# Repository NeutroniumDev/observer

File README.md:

# Observer
Observer is a device that measures the altitude, acceleration, rotation, and location of model rockets. 

As of June 24, 2022, Observer's schematic is complete-ish but untested. It uses the following chips:
- SAMD21G18   (Processing)
- USB-C port (data transfer
  + Protection IC (can be omitted) 
- ISM330         (Rotation and low-acceleration measurements)
- BMP390        (Pressure-based altitude measurements)
- ADXL375          (High-acceleration measurements)
- Micro SD card      (Temporary data storage)
- Ublox MAX M8     (GPS)
  + External LNA
- RFM97C         (LoRa Radio tranceiver)
- PCA9685PW     (LED driver, used as motor driver.)

Future changes (maybe):
-Change the pogo pin pads to headers for easier debugging, and the JTAG pads to
a full JTAG connector.
-Change the logo on the back of the PCB because I won't be using it for the TARC 
competition anymore. 
-Remove the USB-C anti-static protection IC, because it costs money and is most
likely useless.
-Remove a lot of decoupling caps, because I don't really need them
-Find a better way of controlling the servo motors, maybe through connecting them
to GPIO and using a level shifter

**Notes:**

As of June 24th, 2022 the design has not been fully validated. I don't have a 
JTAG debugger and I can't get one right now, so I cant upload a bootloader to upload
code over USB. From what I can tell the voltages look fine and the power management 
works perfectly, but I have not been able to test anything else. Plus, since most of
the schematic is based on reference designs, I see no reason why things *shouldn't*
work. 

To build this for myself I substituted the ISM330 with its non-industrial variant, the
LSM6DSO32. In retrospect I realize that the ISM330 was overkill, and using the LSM6DSO32 
makes the secondary high-g accelerometer redundant in most use cases, since the LSM6 can
already go up to 32G. So, if you're looking to build this for yourself, just get the LSM6
and skip the ADXL375, it will save you ~12 bucks. 

More retrospect: the LNA is probably also not very useful, since when used with
rockets the GPS basically has clear view of the sky with very little blocking the signal, 
apart from maybe the rocket casing, but that's insignificant. If you're building this for yourself, 
you can omit the LNA, but MAKE SURE you change the schematic and board layout so that 
the gps module connects directly to the u.fl connector. The GPS will not work otherwise. 
The LNA also has some really fine pitch pins, so the risk of shorting contacts 
is pretty high. So be careful!

As for the name, 'observer' is staying for now since I can't really think of anything
else. Suggestions would be much appreciated! 

This project is licensed under the GNU General Public License v3.0.
Please use responsibly. You *can* make a missle with this, but that doesn't mean you should.

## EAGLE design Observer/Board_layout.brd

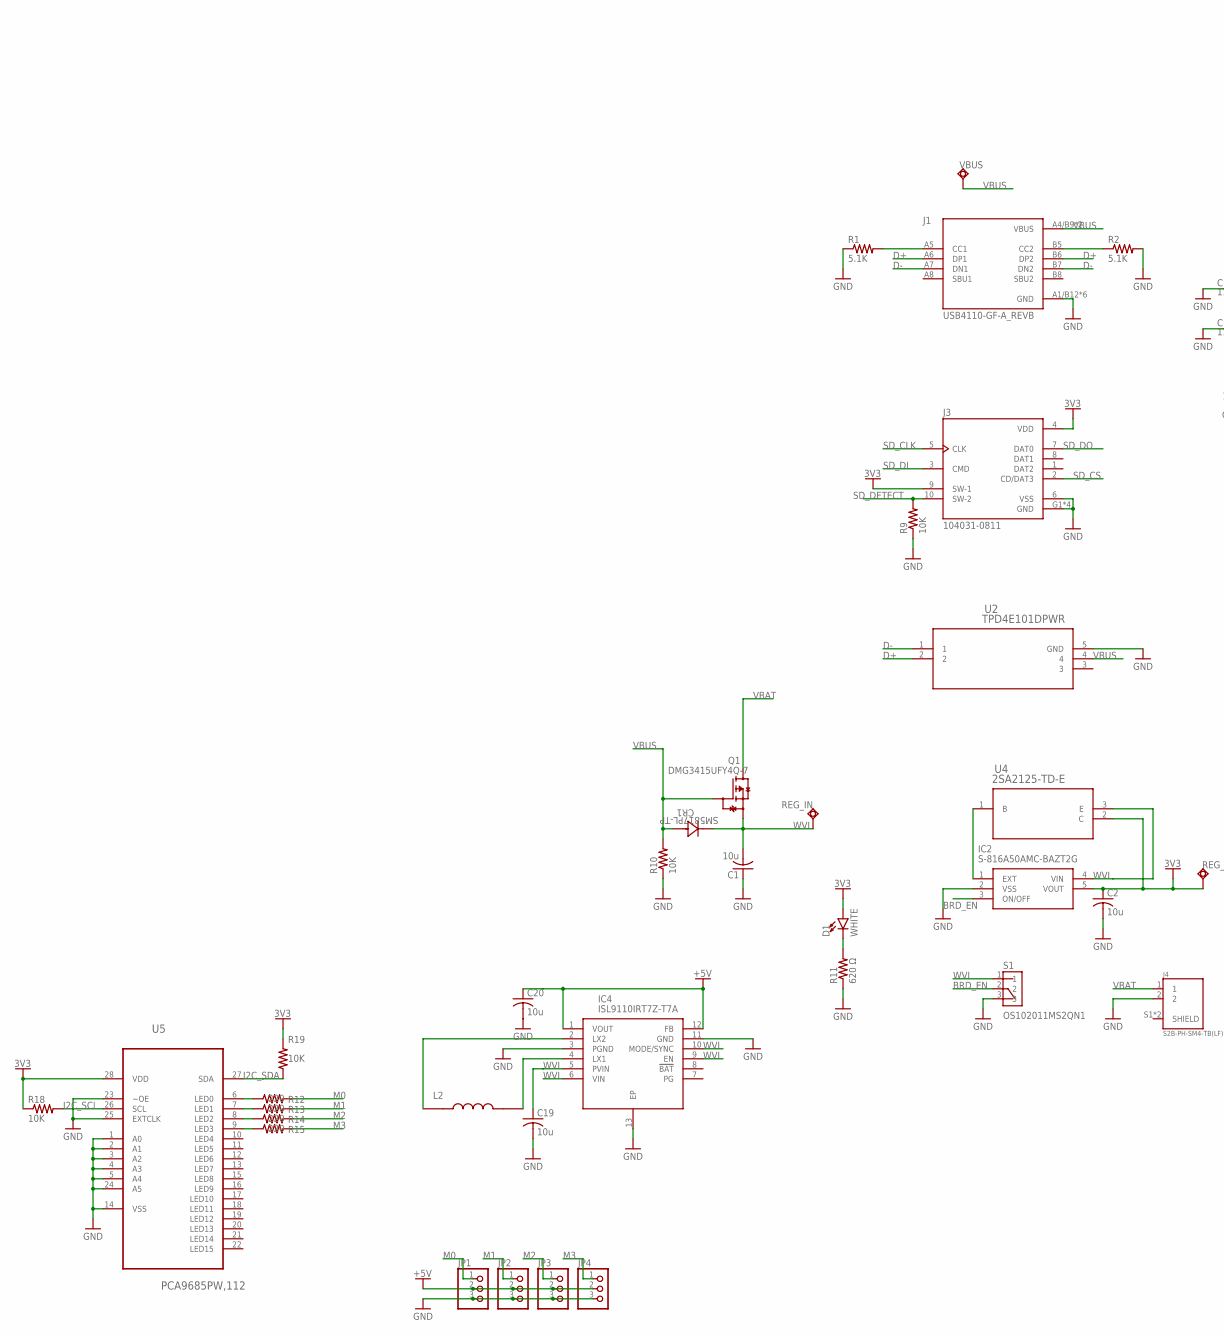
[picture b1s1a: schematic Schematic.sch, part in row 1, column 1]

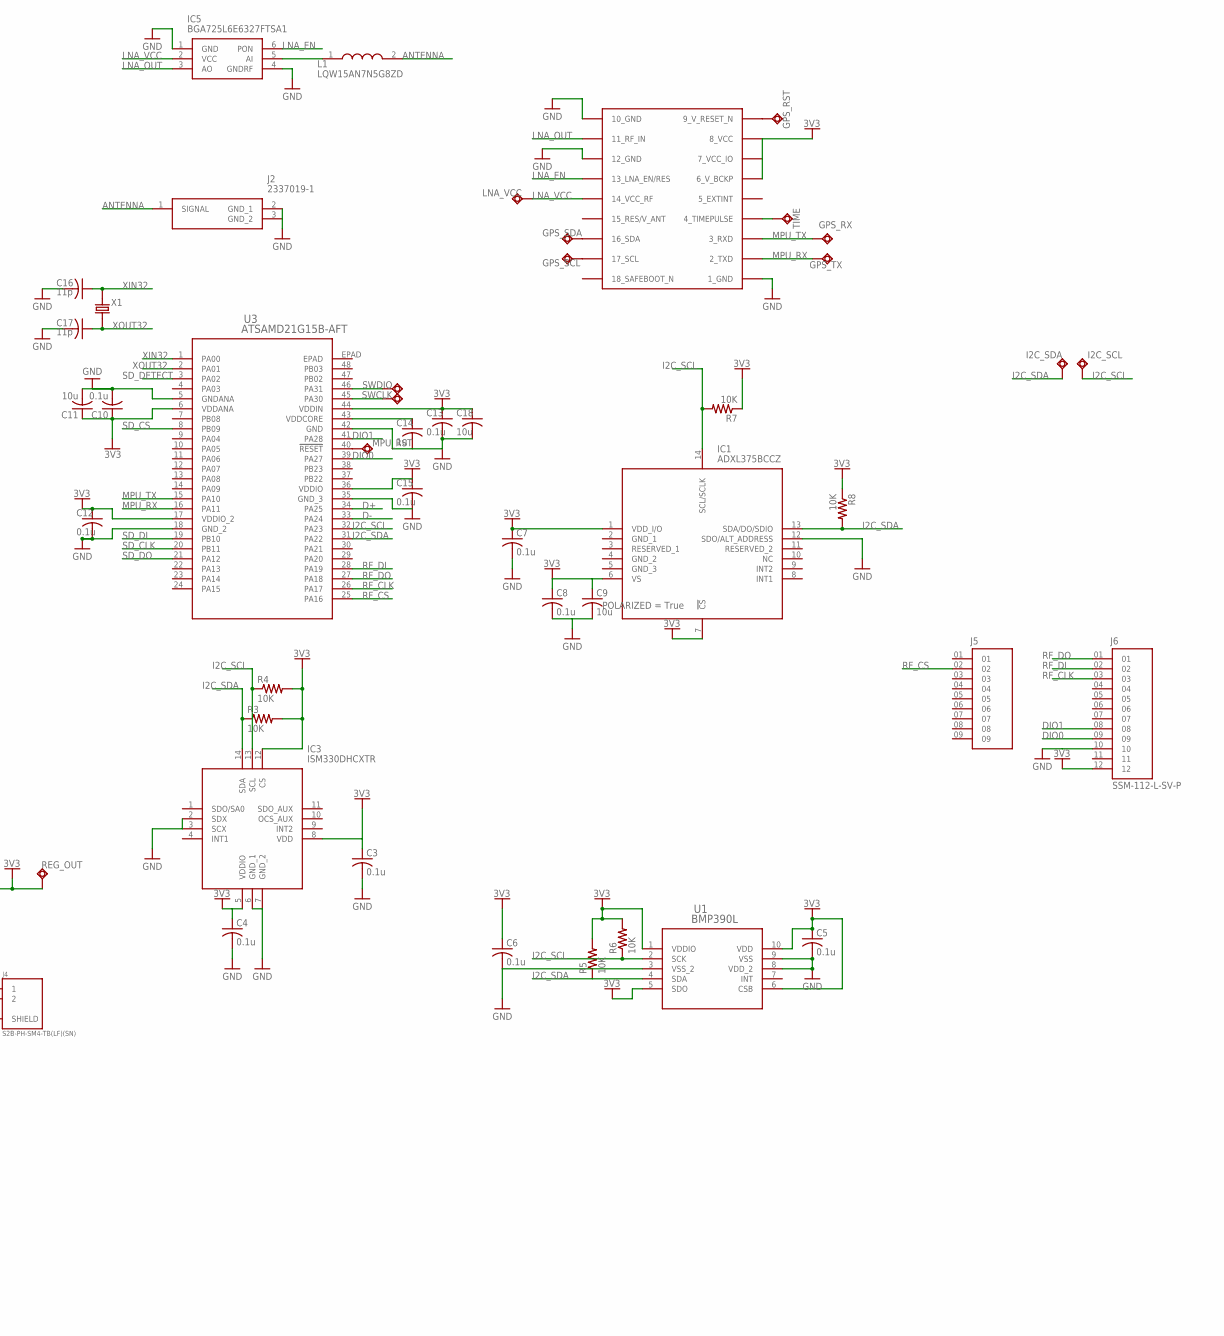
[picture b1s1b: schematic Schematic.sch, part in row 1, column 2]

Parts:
C1, C2, C9, C11: 10u; C0805
C3, C4, C5, C6, C7, C8: 0.1u; C0805
C10, C12, C13, C15: 0.1u; C0603
C14: 1u; C0603
C16, C17: 11p; CAPC1005X60
C18: 10u; C0603
C19, C20: 10u; C0805K
CR1: SM5817PL-TP; CR_5817PL-TP_MCC
D1: WHITE; LED-0603
GPS_RST: TPSQTP20SQ; TP20SQ
GPS_RX: TPSQTP20SQ; TP20SQ
GPS_SCL: TPSQTP20SQ; TP20SQ
GPS_SDA: TPSQTP20SQ; TP20SQ
GPS_TX: TPSQTP20SQ; TP20SQ
I2C_SCL, I2C_SDA: TPSQTP20SQ; TP20SQ
IC1: ADXL375BCCZ; CC-14-1
IC2: S-816A50AMC-BAZT2G; SOT95P275X130-5N
IC3: ISM330DHCXTR; LGA-14(2.5X3X0.86)
IC4: ISL9110IRT7Z-T7A; SON40P300X300X75-13N
IC5: BGA725L6E6327FTSA1; BGS12SN6E6327XTSA1
J1: USB4110-GF-A_REVB; GCT_USB4110-GF-A_REVB
J2: 2337019-1; 23370191
J3: 104031-0811; MOLEX_104031-0811
J4: S2B-PH-SM4-TB(LF)(SN); JST_S2B-PH-SM4-TB(LF)(SN)
J5: SSM-109-L-SV; SAMTEC_SSM-109-L-SV
J6: SSM-112-L-SV-P; SAMTEC_SSM-112-L-SV-P
JP1, JP2, JP3, JP4: PINHD-1X3; 1X03
L1: LQW15AN7N5G8ZD; LQW15CNR20J00B
L2: LQH43PN2R2M26L; IND_LQH43PN2R2M26L
LNA_VCC: TPSQTP20SQ; TP20SQ
MPU_RST: TPSQTP20SQ; TP20SQ
Q1: DMG3415UFY4Q-7; TRANS_DMG3415UFY4Q-7
R1, R2: 5.1K; M0805
R3, R4, R5, R6, R7, R8, R9, R10: 10K; M0805
R11: 620 Ω; R0402
R12, R13, R14, R15: 220; R0805
R18, R19: 10K; R0805
REG_IN: TPSQTP20SQ; TP20SQ
REG_OUT: TPSQTP20SQ; TP20SQ
S1: OS102011MS2QN1; SW_OS102011MS2QN1
SWCLK: TPSQTP20SQ; TP20SQ
SWDIO: TPSQTP20SQ; TP20SQ
TIME: TPSQTP20SQ; TP20SQ
U1: BMP390L; BMP390L_BOS
U2: TPD4E101DPWR; DPW4
U3: ATSAMD21G15B-AFT; TQFP48_7X7MC_MCH
U4: 2SA2125-TD-E; PCP-3_2P5X4P5_ONS
U5: PCA9685PW,112; SOP65P640X110-28N
U$1: MAX-M8
VBUS: TPSQTP20SQ; TP20SQ
X1: ECS-.327-7-34B-TR; XTAL_ECS-.327-7-34B-TR

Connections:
3V3: C2.1, C3.1, C4.1, C5.1, C6.1, C7.1, C8.1, C9.1, C10.1, C11.1, C12.1, C13.1, C15.1, C18.1, D1.A, IC1.1 (VDD_I/O), IC1.6 (VS), IC1.7 (!CS), IC2.5 (VOUT), IC3.5 (VDDIO), IC3.8 (VDD), IC3.12 (CS), J3.4 (VDD), J3.9 (SW-1), J6.12, R3.2, R4.2, R5.2, R6.2, R7.1, R8.1, R18.1, R19.2, REG_OUT.TP, U1.1 (VDDIO), U1.5 (SDO), U1.6 (CSB), U1.10 (VDD), U3.6 (VDDANA), U3.17 (VDDIO_2), U3.36 (VDDIO), U3.44 (VDDIN), U4.2 (C), U5.28 (VDD), U$1.6_V_BCKP, U$1.7_VCC_IO, U$1.8_VCC
+5V: C20.1, IC4.1 (VOUT), IC4.12 (FB), JP1.2, JP2.2, JP3.2, JP4.2
ANTENNA: J2.1 (SIGNAL), L1.2
BRD_EN: IC2.3 (ON/OFF), S1.2
D+: J1.A6 (DP1), J1.B6 (DP2), U2.2, U3.34 (PA25)
D-: J1.A7 (DN1), J1.B7 (DN2), U2.1, U3.33 (PA24)
DIO0: J6.09, U3.39 (PA27)
DIO1: J6.08, U3.41 (PA28)
GND: C1.1, C2.2, C3.2, C4.2, C5.2, C6.2, C7.2, C8.2, C9.2, C10.2, C11.2, C12.2, C13.2, C14.2, C15.2, C16.2, C17.2, C18.2, C19.2, C20.2, IC1.12 (SDO/ALT_ADDRESS), IC2.2 (VSS), IC3.2 (SDX), IC3.3 (SCX), IC3.6 (GND_1), IC3.7 (GND_2), IC4.3 (PGND), IC4.11 (GND), IC4.13 (EP), IC5.1 (GND), IC5.4 (GNDRF), J1.A1/B12 (GND), J1.B1/A12 (GND), J1.S1 (GND), J1.S2 (GND), J1.S3 (GND), J1.S4 (GND), J2.2 (GND_1), J2.3 (GND_2), J3.6 (VSS), J3.G1 (GND), J3.G2 (GND), J3.G3 (GND), J3.G4 (GND), J4.2, J6.10, JP1.3, JP2.3, JP3.3, JP4.3, R1.1, R2.2, R9.1, R10.1, R11.1, S1.3, U1.3 (VSS_2), U1.8 (VDD_2), U1.9 (VSS), U2.5 (GND), U3.5 (GNDANA), U3.18 (GND_2), U3.35 (GND_3), U3.42 (GND), U5.1 (A0), U5.2 (A1), U5.3 (A2), U5.4 (A3), U5.5 (A4), U5.14 (VSS), U5.23 (~OE), U5.24 (A5), U5.25 (EXTCLK), U$1.1_GND, U$1.10_GND, U$1.12_GND
I2C_SCL: I2C_SCL.TP, IC1.14 (SCL/SCLK), IC3.13 (SCL), R4.1, R6.1, R7.2, R18.2, U1.2 (SCK), U3.32 (PA23), U5.26 (SCL)
I2C_SDA: I2C_SDA.TP, IC1.13 (SDA/DO/SDIO), IC3.14 (SDA), R3.1, R5.1, R8.2, R19.1, U1.4 (SDA), U3.31 (PA22), U5.27 (SDA)
LNA_EN: IC5.6 (PON), U$1.13_LNA_EN (13_LNA_EN/RES)
LNA_OUT: IC5.3 (AO), U$1.11_RF_IN
LNA_VCC: IC5.2 (VCC), LNA_VCC.TP, U$1.14_VCC_RF
M0: JP1.1, R12.2
M1: JP2.1, R13.2
M2: JP3.1, R14.2
M3: JP4.1, R15.2
MPU_RX: GPS_TX.TP, U3.16 (PA11), U$1.2_TXD
MPU_TX: GPS_RX.TP, U3.15 (PA10), U$1.3_RXD
unnamed: J1.A5 (CC1), R1.2
unnamed: J1.B5 (CC2), R2.1
unnamed: MPU_RST.TP, U3.40 (!RESET)
unnamed: IC5.5 (AI), L1.1
unnamed: TIME.TP, U$1.4_TIMEPULSE
unnamed: C14.1, U3.43 (VDDCORE)
unnamed: GPS_RST.TP, U$1.9_RESET_N (9_V_RESET_N)
unnamed: IC2.1 (EXT), U4.1 (B)
unnamed: GPS_SDA.TP, U$1.16_SDA
unnamed: GPS_SCL.TP, U$1.17_SCL
unnamed: SWCLK.TP, U3.45 (PA30)
unnamed: SWDIO.TP, U3.46 (PA31)
unnamed: D1.C, R11.2
unnamed: IC4.4 (LX1), L2.2
unnamed: IC4.2 (LX2), L2.1
unnamed: R12.1, U5.6 (LED0)
unnamed: R13.1, U5.7 (LED1)
unnamed: R14.1, U5.8 (LED2)
unnamed: R15.1, U5.9 (LED3)
RF_CLK: J6.03, U3.26 (PA17)
RF_CS: J5.02, U3.25 (PA16)
RF_DI: J6.02, U3.28 (PA19)
RF_DO: J6.01, U3.27 (PA18)
SD_CLK: J3.5 (CLK), U3.20 (PB11)
SD_CS: J3.2 (CD/DAT3), U3.8 (PB09)
SD_DETECT: J3.10 (SW-2), R9.2, U3.3 (PA02)
SD_DI: J3.3 (CMD), U3.19 (PB10)
SD_DO: J3.7 (DAT0), U3.21 (PA12)
VBAT: J4.1, Q1.3 (D)
VBUS: CR1.2, J1.A4/B9 (VBUS), J1.B4/A9 (VBUS), Q1.1 (G), R10.2, U2.4, VBUS.TP
WVI: C1.2, C19.1, CR1.1, IC2.4 (VIN), IC4.5 (PVIN), IC4.6 (VIN), IC4.9 (EN), IC4.10 (MODE/SYNC), Q1.2 (S), REG_IN.TP, S1.1, U4.3 (E)
XIN32: C16.1, U3.1 (PA00), X1.2
XOUT32: C17.1, U3.2 (PA01), X1.1

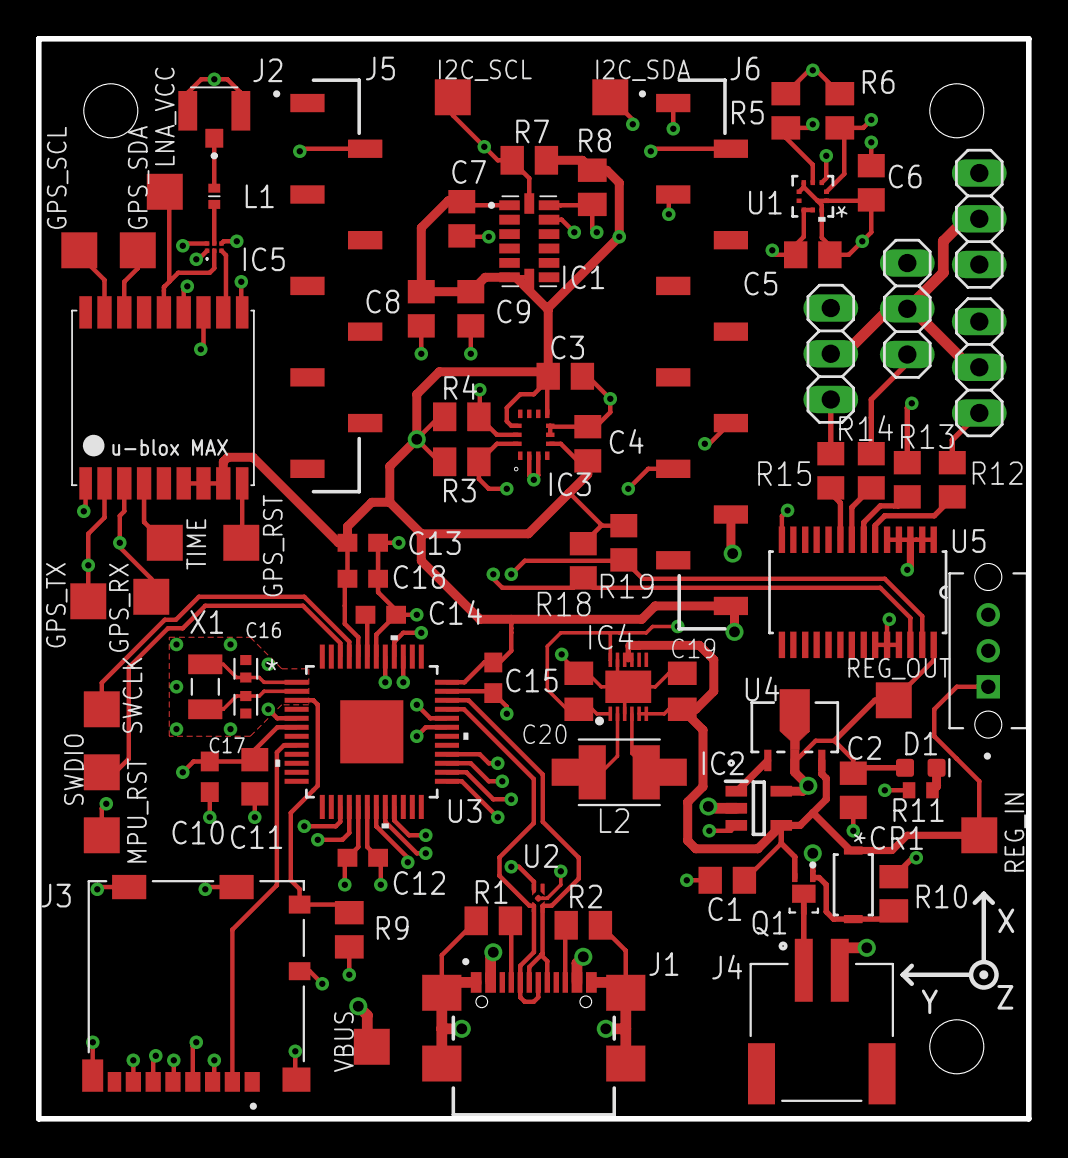
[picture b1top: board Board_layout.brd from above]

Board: 4 copper layers, 55.0 x 60.0 mm, 81 parts (0 on the bottom side), 53 nets.

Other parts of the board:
E$1: LOGO

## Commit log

2022-06-24 Create LICENSE.txt (#1)

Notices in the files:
parts and their libraries:
SparkFun-LED: Licensing: Creative Commons ShareAlike 4.0 International - https://creativecommons.org/licenses/by-sa/4.0
COPYRIGHT: Copyright (C) 2022 Ultra Librarian. All rights reserved.
COPYRIGHT: Copyright (C) 2021 Ultra Librarian. All rights reserved.
